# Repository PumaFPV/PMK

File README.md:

# Puma Mechanical Keyboard
PMK - a full wireless HID ecosystem for split keyboards and other fun devices

The goal is to make a suit of wireless devices such as "smart keyboard" (combined mouse and keyboard), gamepad, LEDs, knobs, display, etc  
The first step is to make a wireless split keyboard, and then we will see later...

Currently, you can connect up to 8 (software limited) devices per dongle, each of them having up to 8 (software limited) layers. Layers only affect keyboards and LED.

## Dongle
The dongle is "master" ESP32S2/S3, appears as HID (keyboard, mouse and joystick) and as Mass Storage device Class with config files inside.
Maybe also store password manager later...

As the dongle is the master of PMK, it hosts the config files for each devices. Here is the expected file organisation:

		|--deviceName1  
		|  |- deviceName1.json  
		|  |--keyboard  
		|  |  |- kb-l1.json  
		|  |  |- kb-l2.json  
		|  |--led  
		|  |  |- led-l1.json  
		|  |  |- led-l2.json  
		|--deviceName2  
		|  |- deviceName2.json  
		|  |--keyboard  
		|  |  |- kb-l1.json  
		|  |  |- kb-l2.json  

Exemple file structure can be found [here](https://github.com/PumaFPV/PMK/tree/main/Software/PMK_dongle/data/leftKB) 

For more details about devices configurations / capabilities check the [Protocol](https://github.com/PumaFPV/PMK?tab=readme-ov-file#protocols) chapter.

### Keyboard config file - HID codes
Check out the [PMK HID keyboard keycodes.md](https://github.com/PumaFPV/PMK/blob/main/PMK%20HID%20keyboard%20keycodes.md) for more information on which code corresponds to which key.

## Devices
Can run on any espressif chip that can run ESP-NOW. (I will later add support for nRF52 chips for lower power consumption, but it will be incompatible with ESP32 hardware)
The plan is to run the simplest firmware on all devices and being able to configure them via their corresponding .json files on the master dongle. 
Each device should be configurable via UART (set device ID, set dongle MAC address, and read device MAC address). 
See sample [device code](https://github.com/PumaFPV/PMK/tree/main/Software/PMK_device) for example. (Needs an update)

### Keyboard
For example a keyboard would send pressed keys number "0x04, 0xA1", which the dongle then reads in the .json as coordinates for returning desired key "a,b", if special key is pressed (volume up, brighntess control...) then do the appropriate consummer control action.
Keys are read with 74HC165 shift registers so theoratically you could have A LOT of keys per keyboard. Current limitation is the max value of keyID which is 255, so there could be a maximum of 255 keys per keyboard (+8 layers...).
For more information about the hardawre, check the [hardware](https://github.com/PumaFPV/PMK/tree/main?tab=readme-ov-file#hardware) section.
A casing is being designed, it is 3D printable. As foam grid is put inside for better sound (I think it is better?). 
It support module on the thumb side ([Circle trackpad](https://www.cirque.com/glidepoint-circle-trackpads) and [3D mouse](https://hackaday.io/project/187172-os3m-mouse)). Both modules have been tested and work. See [Space mouse](https://github.com/PumaFPV/PMK/tree/main?tab=readme-ov-file#space-mouse) section for more info.

### Mouse
Mouse can send x,y movement, wheel, pan scrolling and mouse buttons (left, middle, right, forward, backward). Each button is encoded as a bit in the "key" byte of the packet.
No configuration needed on the dongle appart from the DPI setting.
I plan on retro fitting a wired Logitech G300 with PMK so that it frees up a USB port + becomes wireless. It will be a great first POC. I also have a M330 laying around. It might also end up as a PMK mouse.

### Gamepad
Gamepad can send 2 analog joysticks, 2 analog triggers, dpad buttons, and 32 additionnal buttons. No additionnal configuration needed on the dongle.
I current upgraded an old thrustmaster sim set (FCS & WCS) from 1992 with PMK. They used to have an ADB port, but now both are fully wireless and appear as one gamepad on the computer. The update is a bit crude as it was first though as a POC for trying out the gamepad feature. But since it works fine, I kept it this way.

### LED
(For release 1.2.0)
Hopefully processing key press and led function on dongle and send data to device is fast enough, otherwise I will have to run led function on keyboard. (TODO)
Buildin keyboard functions: all kb, breath, swipe wave (single color or rainbow), key wave, single key... (TODO / Partially implemented...)
Uses the WS2812 kind of LED IC.

### Knob
Knobs are in absolute position going from 0 to 255. Could be used for Deej (now only used for deej).

For encoder knobs, this is handled on the device, so it can enumerate as a keyboard pressing one key for clockwise and another for counterclockwise rotation. But it could also be treated as an absolute position depending on the device software.

### Space mouse
The software is mostly inspired from [Magellan](https://github.com/jfedor2/magellan-spacemouse/tree/master) and from reports analysed from a 3DConnexion Space mouse with [hid-tool](https://gitlab.freedesktop.org/libevdev/hid-tools). 
The current electronics and plastics hardware are from [OS3M mouse](https://hackaday.io/project/187172-os3m-mouse) and it works well. The software still needs some adjustements for calibration.
Note: If standard VIK connector is needed, PCB has to be flipped. No special hardware modifications are needed.

## Protocols

### ESP-NOW - Device to Dongle
This is the packet sent via ESP-NOW. 
Packet structure is: 
| Byte | 1 | 2 | 3-16 |
| ---- | - | - | - |
| Description | DeviceID | PacketID | Payload |

The goal of this packet strucure is that the dongle knows who is sending data and what kind of data to expect from the payload.
The deviceID is mostly used for keyboards and mouse to use the corresponding config files.

the payload's goal is to send data as simple as possible, e.g. keyboard sends key IDs pressed (max 8 at a time) and then the dongle processes the key ID depending on the json configuration

| Packet ID | Packet type | Packet information | Number of bytes | Example packet | Example description |
| --------- | ----------- | ------------------ | --------------- | -------------- | ------------------- |
| 0x00 | Telemetry | Send battery voltage, temperature, mac address, errors... | 15 | dID 00 battery temperature address[6] err err err err err |  |
| 0x01 | Keyboard | 1 byte = 1 key ID | 8 | dID 01 A2 34 DB 32 21 4F 00 00 | 6 keys are pressed |
| 0x02 | Mouse | move x, move y, wheel, pan, mouse clicks | 7 | dID 02 xx yy ww pp kk |move x relative, move y relative, move w relative, move p relative, kk key press|
| 0x03 | Gamepad | 2 joysticks, 2 analog triggers, 9 directions d pad, 32 buttons | 12 | dID 03 xx yy zz rz rx ry hh bb bb bb bb bb |  |
| 0x04 | LED | Choose pre defined function, and R, G and B | 8 | dID 04 func ledNumberStart ledNumberEnd Red Green Blue |  |
| 0x05 | Knob / Rotary encoder / potentiometer | each byte is a pot value, max 8 pot per MCU | 10 | dID 05 FF 00 FF 00 FF 00 FF 00 | 4 pots are at max, 4 are at min |
| 0x06 | Actuator | Choose command type (torque, speed, position) | 5 | dID 06 01 |  |
| 0x07 | Display | send image to display using wifi for faster refresh rate? or store on local mem | 6 | dID 07 imgNumber x y brightness | Display img number n at coordinates x,y and brightness b. Might change later |
| 0x08 | Serial | send up to 8 bytes of data | 10 | dID 08 aa bb cc dd ee ff gg hh | Sending 8 bytes of data |
| 0x09 | SpaceMouse | send 3 bytes for translation (x, y, z) and 3 bytes for rotation (x, y, z), signed intergers | 6 | dID 7F 00 00 FF 00 00 | Positive translation on x and negative rotation on x |

### Serial config - Dongle to PC
The dongle supports a few serial commands, they only consist of a string, no CR/LF should be send or the command won't be recongnised. (The received command is hashed into a number then switched cased to the correct function)
Here is the list of supported commands:
  - h / help : display available commands
  - info : display all info
  - macaddress / getmacaddress : display dongle MAC address
  - version : display build date and version
  - power : display RF Tx power
  - cpu : display cpu info
  - format : format file system
  - restart / reboot : restart the dongle
  - deej : toggle on / off deej
  - config / load: Reload configuration files
  - l0 / l1 / l2... : Force the current layer to... If one keybind moves to new layer it will be ignored use l-1 command to reset force layer
  - l-1 : disable forced layer
  - debug1 / debug2... : Toggle debug output. Different kind of debug available

### Serial config - Device to PC
Before being able to communicate with the dongle, the device has to know the dongle MAC address, and must own a deviceID. You will also need to know the device MAC address to give it to the dongle.
Here is the list of supported commands:
- h / help : returns available commands
- info : display all info
- macaddress / getmacaddress : returns device MAC address
- setdonglemacaddress : update dongle MAC address, be sure to send values in HEX mode
- getdonglemacaddress : returns the current dongle MAC address
- setdeviceid : update deviceID to new value
- getdeviceid : returns currently set devi
- version : returns build date and version
- power : returns RF Tx power
- cpu : returns CPU info
- setcpufreq : set new CPU frequency
- restart : restart the dongle
- scan : Scan for side module presence
- debug1 / debug2... : Toggle debug output. Different kind of debug available

## Hardware
### The dongle
Dongle is still HW00 (first rev), it needs 3 small patches to work properly. A [HW01](https://github.com/PumaFPV/PMK/tree/main/Hardware/PMK_Dongle/PMK_Dongle_HW01) is designed but hasn't been ordered yet.
The ESP32S2 has some limitations, so a ESP32S3 dongle is being made too [here](https://github.com/PumaFPV/PMK/tree/main/Hardware/PMK_Dongle/PMK_Dongle_S3_HW00).

Even a nRF52 dongle might be made... Who knows[?](https://github.com/PumaFPV/PMK/tree/main/Hardware/PMK_Dongle/PMK_Dongle_C_nRF_HW00)

### The keyboard
As of today the keyboard is at the HW02 stage, and uses the sofle layout (which I do like). It uses 29 hot swappable Kailh Choc switches + one rotary encoder. The MCU is a [PSoM module](https://github.com/PumaFPV/PSoM) (homemade SoM) with an ESP32S2 inside. The SoM allows for quick swap of different MCU to try out different feature. Today the ESP32S2 is used for the ease of software developpement. Its power consumption is bad I am aware. But at least software works.
Here is the changelog.

| HW rev | change list |
| ------ | ----------- |
| HW00   | Based on moonlander layout, integrated ESP32, used as a proof of concept, didn't like the layout in the end |
| HW01   | Based on Sofle, PSoM connector (swappable uC for futur proofing), added rotary encoder, way better layout in my opinion. Added side connector option for trackpad or space mouse |
| HW02   | Still soffle, added support for kailh choc V2 (failed), moved the rotary encoder up, added debouncing for rotary encoder, fixed the side module connector, moved test point to accessible location, updated PSoM pinout for better compatibility |
| HW03 (WIP)  | Still soffle, fixed the silkscreen, Added slot for dongle, fixed V2 footprint, magnetic pogo module? |

More info on [Notion](https://swamp-zydeco-907.notion.site/PumaKeyBoard-b41d42fec8c74b02bc73637fae3648d7)

### Edit the PCBs
If you want to make your own keyboard, or visualize current dongle, keyboard or other devices you will need KiCAD 8 and Component_lib which is my own components library. It can be found in its [own repo](https://github.com/PumaFPV/Component_lib), information on own to install it can be found there.

# Building 
This whole project is built using PlatformIO on VS Code / VS Codium. (If using VS Codium note that the marketplace for extensions doesn't really work, you will need to download cpp and platformIO .vsix extension files from https://marketplace.visualstudio.com/vscode)

Once this is installed you can clone PMK's repo ````git clone https://github.com/PumaFPV/PMK````
and open whichever code you want to build / modify: ````PMK/Software/PMK_keyboard```` with platformIO "Open project".

Once project is opened and loaded (might take a few minutes for the first time) (it needs internet connection to download library and toolchain) you can compile with ````ctrl + shift + B```` or ````ctrl + shift + U```` to compile and upload, or use the bottom ribbon (make sure to select the correct workspace before compiling and uploading).

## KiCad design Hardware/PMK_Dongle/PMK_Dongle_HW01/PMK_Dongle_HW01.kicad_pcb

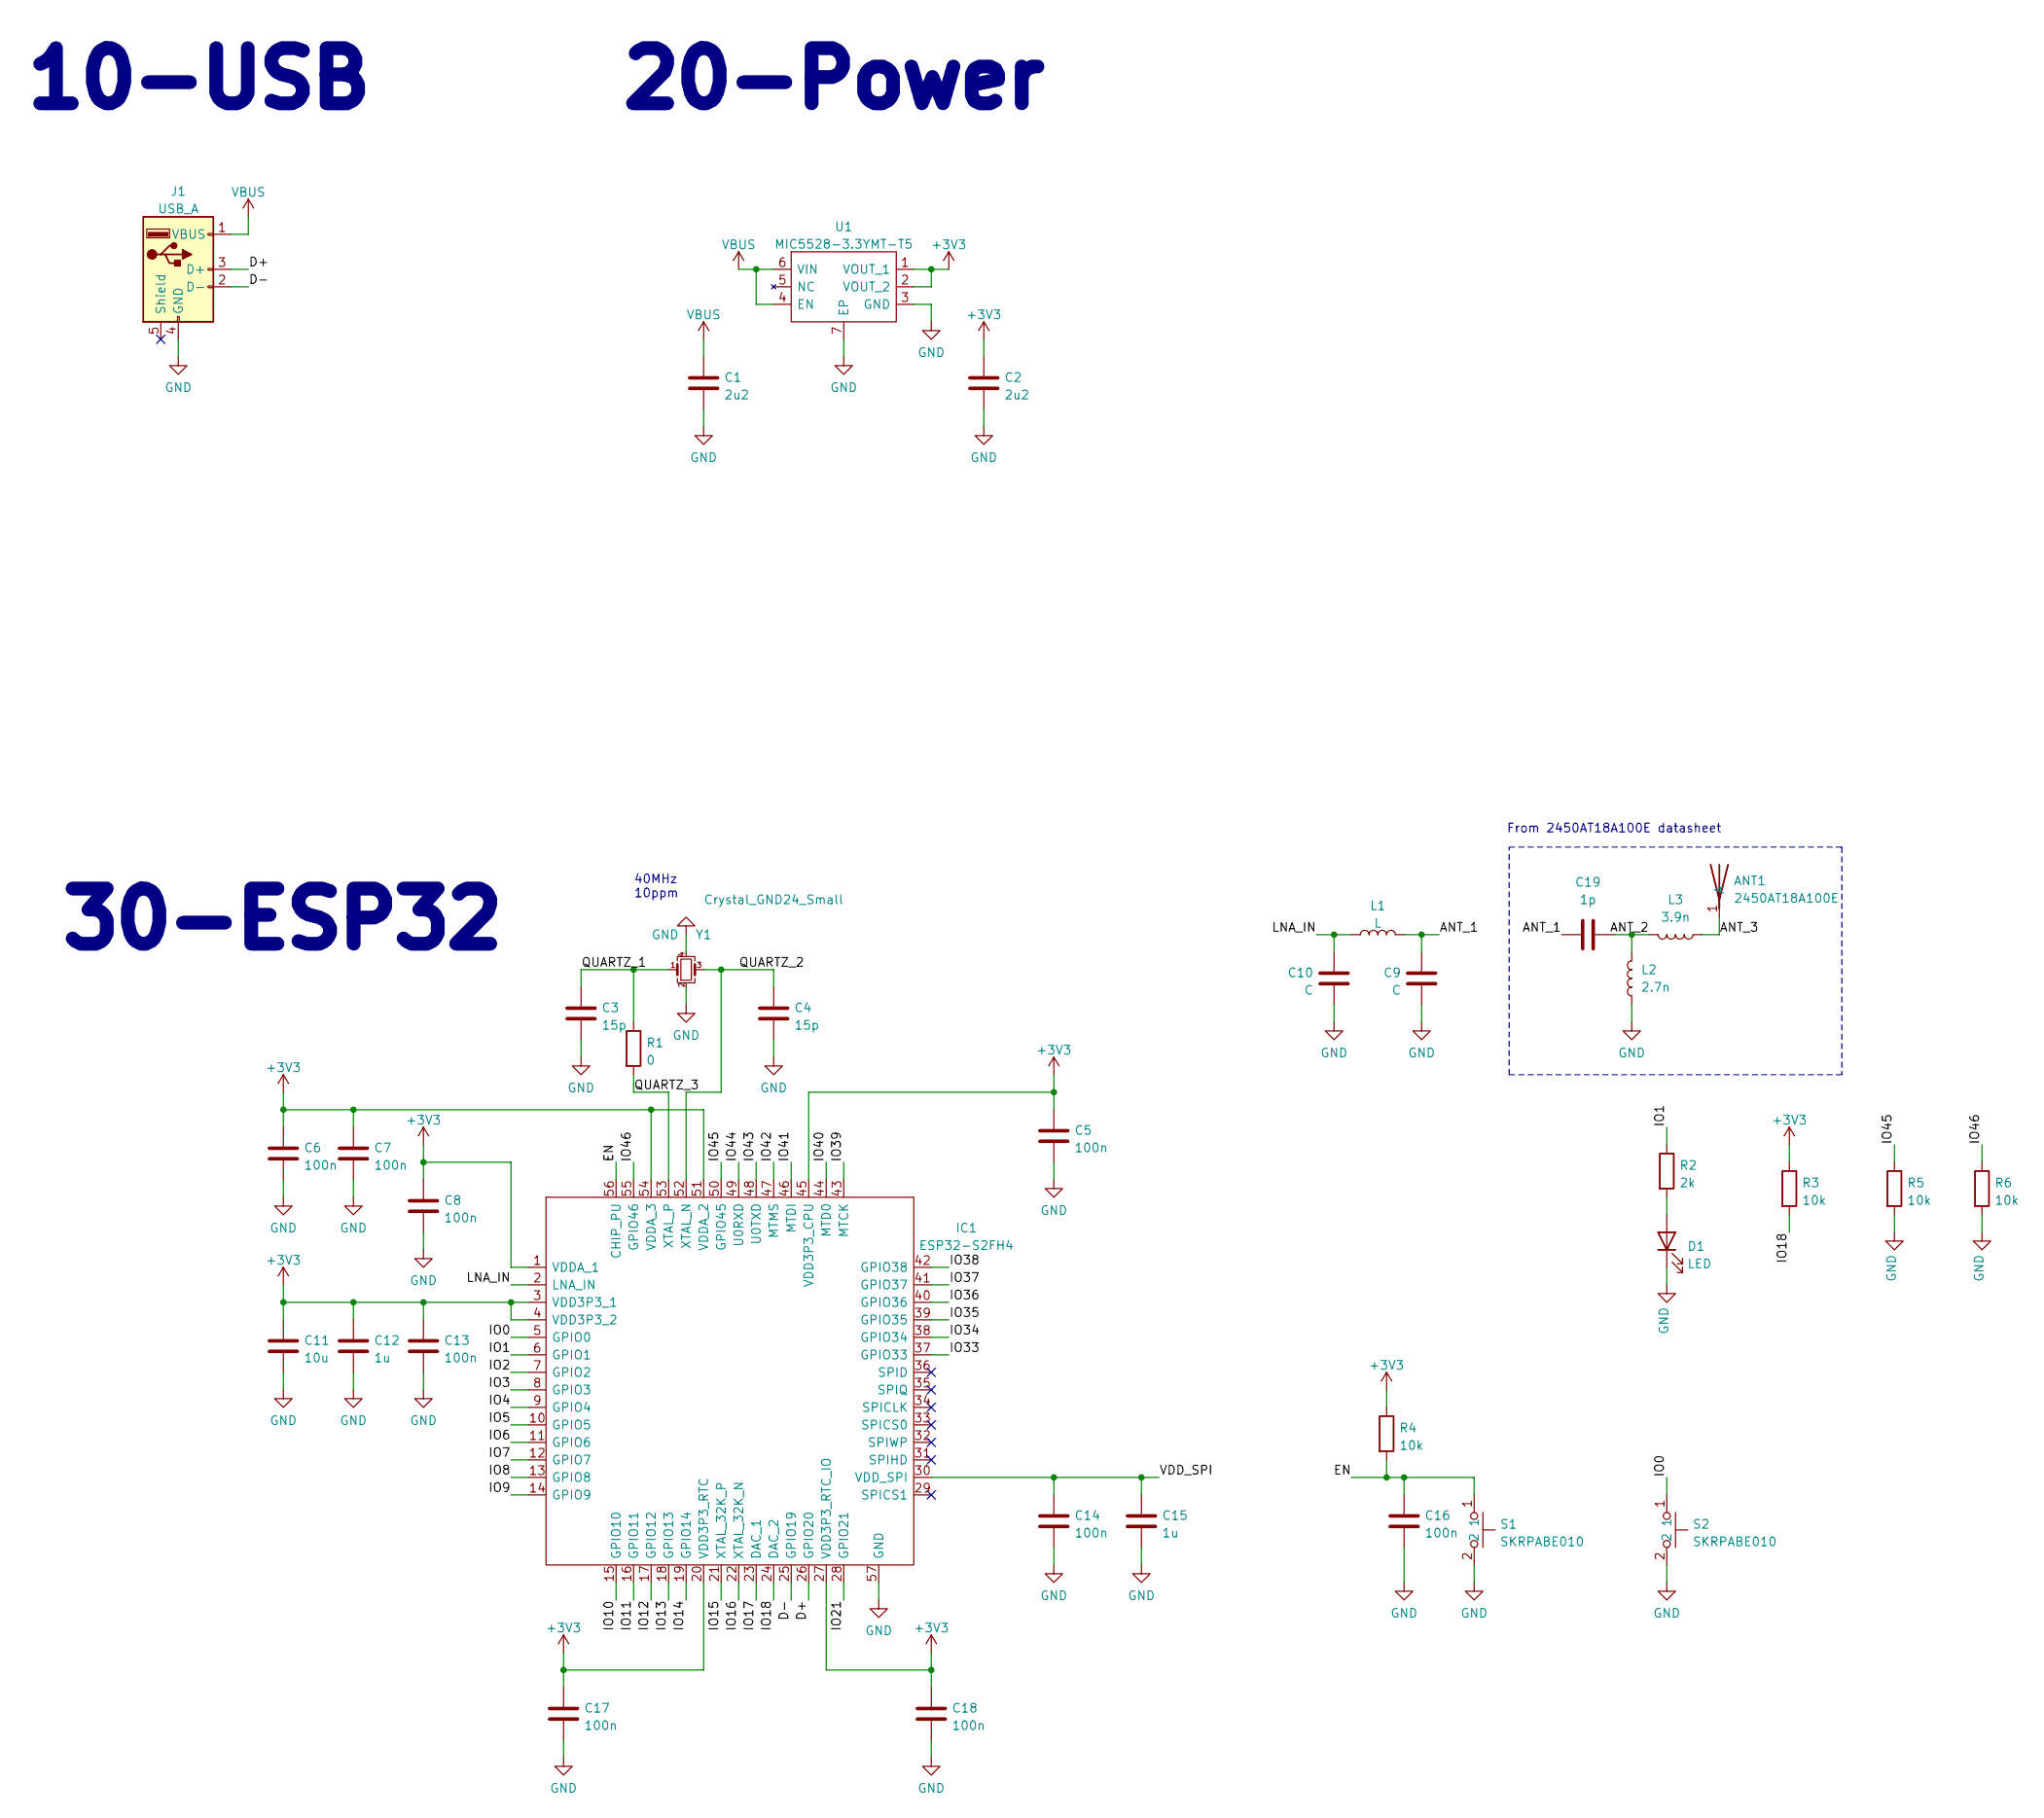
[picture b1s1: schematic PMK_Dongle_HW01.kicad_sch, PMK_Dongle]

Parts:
ANT1: 2450AT18A100E; ANTC3216X140N; Mouser Part Number 609-2450AT18A100E
C1, C2: 2u2; C_0603_1608Metric
C3, C4: 15p; C_0201_0603Metric
C5, C6, C7, C8, C13, C14, C16, C17, C18: 100n; C_0402_1005Metric
C9, C10: C; C_0201_0603Metric
C11: 10u; C_0603_1608Metric
C12, C15: 1u; C_0402_1005Metric
C19: 1p; C_0402_1005Metric
D1: LED; LED_0402_1005Metric
IC1: ESP32-S2FH4; QFN40P700X700X90-57N-D; Mouser Part Number 356-ESP32-S2FH4
J1: USB_A; USB_PCB
L1: L; L_0201_0603Metric
L2: 2.7n; L_0402_1005Metric
L3: 3.9n; L_0402_1005Metric
R1: 0; R_0201_0603Metric
R2: 2k; R_0402_1005Metric
R3, R4, R5, R6: 10k; R_0201_0603Metric
S1, S2: SKRPABE010; B3U-1000P; Mouser Part Number 688-SKRPAB
U1: MIC5528-3.3YMT-T5; SON40P120X120X60-7N-D; Mouser Part Number 998-MIC5528-3.3YMTT5
Y1: Crystal_GND24_Small; Crystal_SMD_2016-4Pin_2.0x1.6mm

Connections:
+3V3: C2.1, C5.1, C6.1, C7.1, C8.1, C11.1, C12.1, C13.1, C17.1, C18.1, IC1.1 (VDDA_1), IC1.3 (VDD3P3_1), IC1.4 (VDD3P3_2), IC1.20 (VDD3P3_RTC), IC1.27 (VDD3P3_RTC_IO), IC1.45 (VDD3P3_CPU), IC1.51 (VDDA_2), IC1.54 (VDDA_3), R3.1, R4.1, U1.1 (VOUT_1), U1.2 (VOUT_2)
/ANT_1: C9.1, C19.2, L1.1
/ANT_2: C19.1, L2.1, L3.1
/ANT_3: ANT1.1 (A), L3.2
/D+: IC1.26 (GPIO20), J1.3 (D+)
/D-: IC1.25 (GPIO19), J1.2 (D-)
/EN: C16.1, IC1.56 (CHIP_PU), R4.2, S1.1
/IO0: IC1.5 (GPIO0), S2.1
/IO1: IC1.6 (GPIO1), R2.1
/IO2: IC1.7 (GPIO2)
/IO3: IC1.8 (GPIO3)
/IO4: IC1.9 (GPIO4)
/IO5: IC1.10 (GPIO5)
/IO6: IC1.11 (GPIO6)
/IO7: IC1.12 (GPIO7)
/IO8: IC1.13 (GPIO8)
/IO9: IC1.14 (GPIO9)
/IO10: IC1.15 (GPIO10)
/IO11: IC1.16 (GPIO11)
/IO12: IC1.17 (GPIO12)
/IO13: IC1.18 (GPIO13)
/IO14: IC1.19 (GPIO14)
/IO15: IC1.21 (XTAL_32K_P)
/IO16: IC1.22 (XTAL_32K_N)
/IO17: IC1.23 (DAC_1)
/IO18: IC1.24 (DAC_2), R3.2
/IO21: IC1.28 (GPIO21)
/IO33: IC1.37 (GPIO33)
/IO34: IC1.38 (GPIO34)
/IO35: IC1.39 (GPIO35)
/IO36: IC1.40 (GPIO36)
/IO37: IC1.41 (GPIO37)
/IO38: IC1.42 (GPIO38)
/IO39: IC1.43 (MTCK)
/IO40: IC1.44 (MTD0)
/IO41: IC1.46 (MTDI)
/IO42: IC1.47 (MTMS)
/IO43: IC1.48 (U0TXD)
/IO44: IC1.49 (U0RXD)
/IO45: IC1.50 (GPIO45), R5.1
/IO46: IC1.55 (GPIO46), R6.1
/LNA_IN: C10.1, IC1.2 (LNA_IN), L1.2
/QUARTZ_1: C3.1, R1.1, Y1.1
/QUARTZ_2: C4.1, IC1.52 (XTAL_N), Y1.3
/QUARTZ_3: IC1.53 (XTAL_P), R1.2
/VDD_SPI: C14.1, C15.1, IC1.30 (VDD_SPI)
GND: C1.2, C2.2, C3.2, C4.2, C5.2, C6.2, C7.2, C8.2, C9.2, C10.2, C11.2, C12.2, C13.2, C14.2, C15.2, C16.2, C17.2, C18.2, D1.1 (K), IC1.57 (GND), J1.4 (GND), L2.2, R5.2, R6.2, S1.2, S2.2, U1.3 (GND), U1.7 (EP), Y1.2, Y1.4
unnamed: D1.2 (A), R2.2
VBUS: C1.1, J1.1 (VBUS), U1.4 (EN), U1.6 (VIN)

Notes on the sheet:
From 2450AT18A100E datasheet
10-USB
30-ESP32
40MHz 10ppm
20-Power

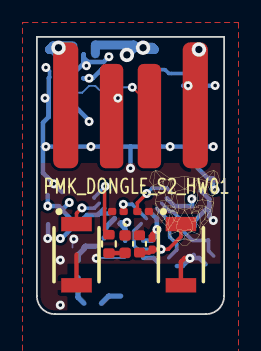
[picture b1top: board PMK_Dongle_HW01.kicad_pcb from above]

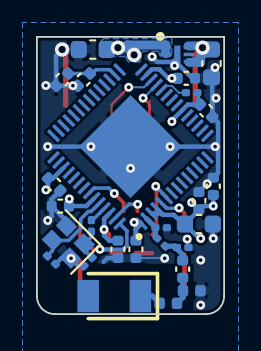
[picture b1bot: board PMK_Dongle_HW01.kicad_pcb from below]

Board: 4 copper layers, 10.4 x 15.4 mm, 36 parts (27 on the bottom side), 20 nets.

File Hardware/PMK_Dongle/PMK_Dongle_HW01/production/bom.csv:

Designator,Footprint,Quantity,Value,LCSC Part #
ANT1,ANTC3216X140N,1,2450AT18A100E,
C1,0603,1,10u,
C10,0201,1,C,
C11,0603,1,10u,
C12,0402,1,1u,
C13,0402,1,100n,
C14,0402,1,100n,
C15,0402,1,1u,
C16,0402,1,100n,
C17,0402,1,100n,
C18,0402,1,100n,
C2,0603,1,10u,
C3,0201,1,15p,
C4,0201,1,15p,
C5,0402,1,100n,
C6,0402,1,100n,
C7,0402,1,100n,
C8,0402,1,100n,
C9,0201,1,C,
D1,0402,1,LED,
IC1,QFN40P700X700X90-57N-D,1,ESP32-S2FH4,
J1,USB_PCB,1,USB_A,
L1,0201,1,L,
R1,0201,1,0,
R2,0402,1,2k,
R3,0201,1,10k,
R4,0402,1,10k,
"S1, S2",SKRPABE010,2,SKRPABE010,
U1,SON40P120X120X60-7N-D,1,MIC5528-3.3YMT-T5,
Y1,Crystal_SMD_2016-4Pin_2.0x1.6mm,1,Crystal_GND24_Small,

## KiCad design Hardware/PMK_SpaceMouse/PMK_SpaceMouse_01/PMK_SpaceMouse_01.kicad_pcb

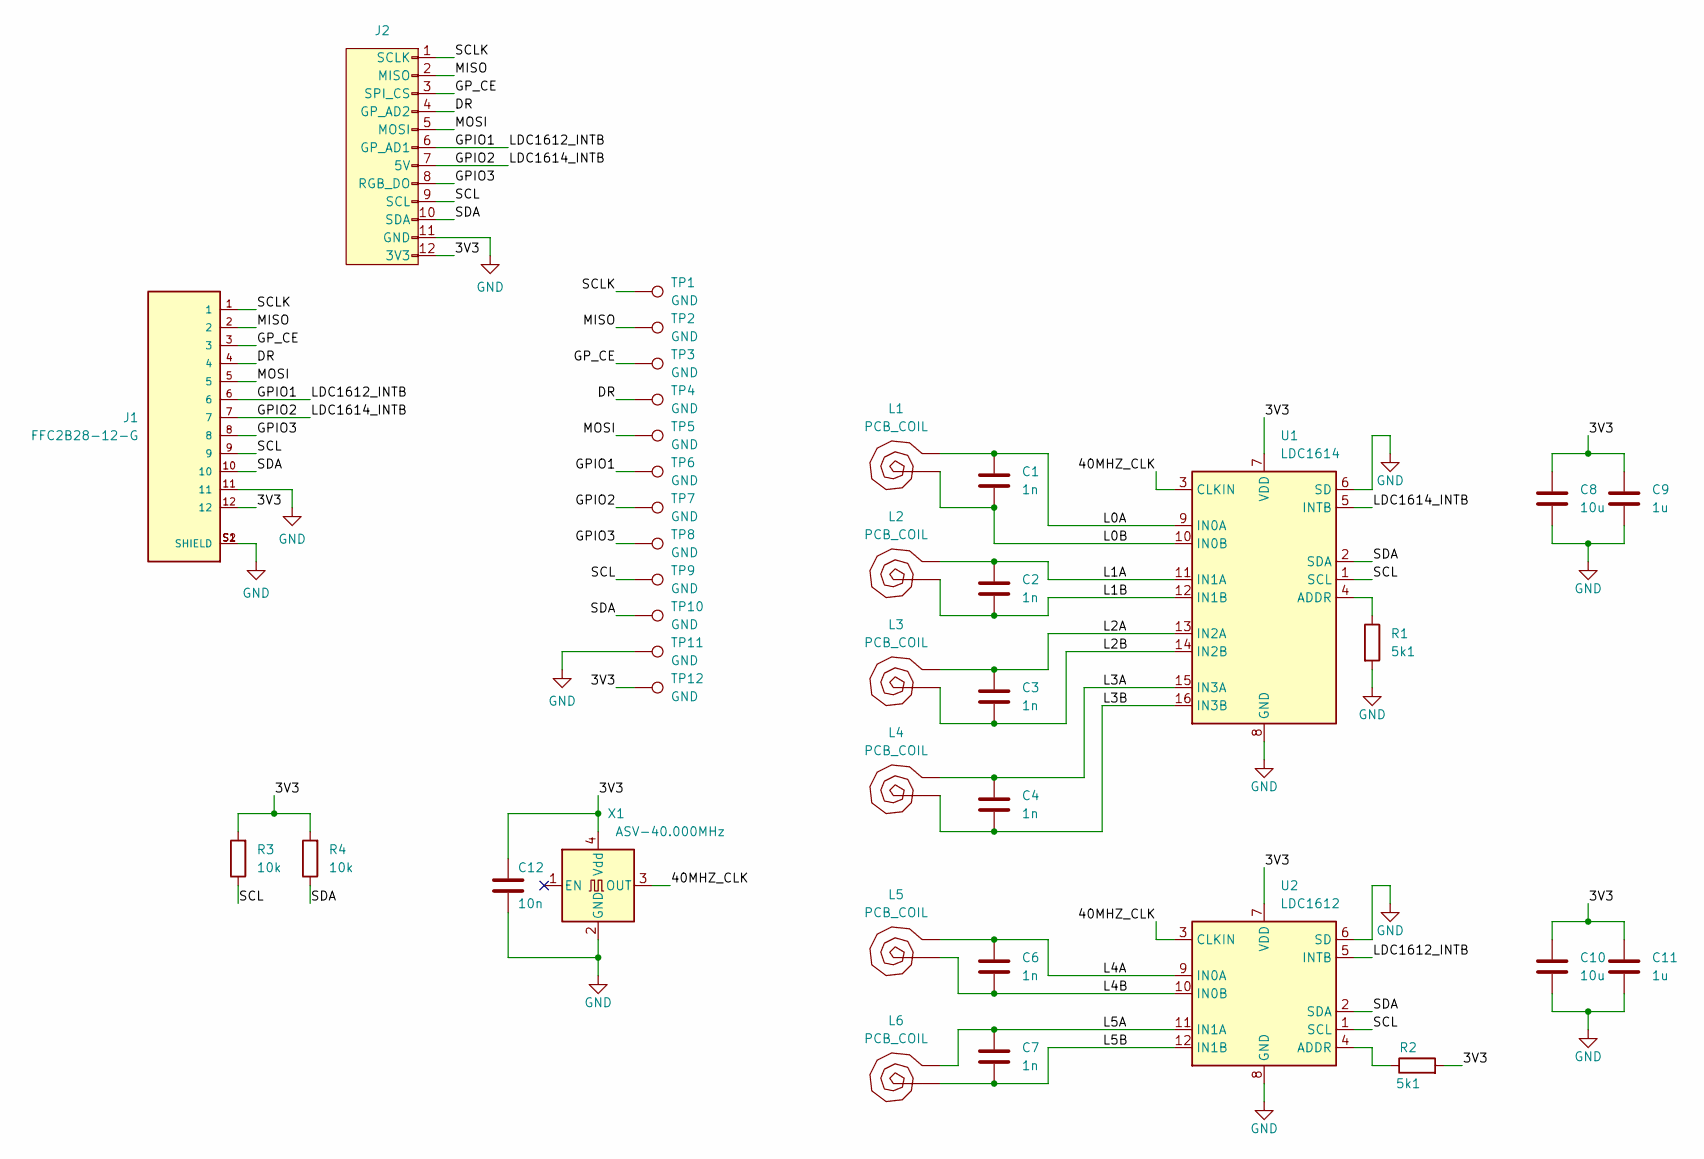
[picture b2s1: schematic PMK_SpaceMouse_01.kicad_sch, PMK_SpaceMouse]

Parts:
C1, C2, C3, C4, C6, C7: 1n; C_0402_1005Metric
C8, C10: 10u; C_0402_1005Metric
C9, C11: 1u; C_0402_1005Metric
C12: 10n; C_0402_1005Metric
J1: FFC2B28-12-G; GCT_FFC2B28-12-G; PARTREV A; DigiKey_Part_Number 2073-FFC2B28-12-GTR-ND
J2: vik-module-connector; vik-module-connector-horizontal
L1, L2, L3, L4, L5, L6: PCB_COIL; COIL_PCB
R1, R2: 5k1; R_0402_1005Metric
R3, R4: 10k; R_0402_1005Metric
TP1, TP2, TP3, TP4, TP5, TP6, TP7, TP8, TP9, TP10, TP11, TP12: GND; TestPoint_Pad_D1.5mm
U1: LDC1614; WQFN-16-1EP_4x4mm_P0.5mm_EP2.6x2.6mm
U2: LDC1612; WSON-12-1EP_4x4mm_P0.5mm_EP2.6x3mm
X1: ASV-40.000MHz; Oscillator_SMD_Abracon_ASV-4Pin_7.0x5.1mm

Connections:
/3V3: C8.1, C9.1, C10.1, C11.1, C12.1, J1.12, J2.12 (3V3), R2.2, R3.2, R4.2, TP12.1, U1.7 (VDD), U2.7 (VDD), X1.4 (Vdd)
/40MHZ_CLK: U1.3 (CLKIN), U2.3 (CLKIN), X1.3 (OUT)
/DR: J1.4, J2.4 (GP_AD2), TP4.1
/GPIO1: J1.6, J2.6 (GP_AD1), TP6.1, U2.5 (INTB)
/GPIO2: J1.7, J2.7 (5V), TP7.1, U1.5 (INTB)
/GPIO3: J1.8, J2.8 (RGB_DO), TP8.1
/GP_CE: J1.3, J2.3 (SPI_CS), TP3.1
/L0A: C1.1, L1.1, U1.9 (IN0A)
/L0B: C1.2, L1.2, U1.10 (IN0B)
/L1A: C2.1, L2.1, U1.11 (IN1A)
/L1B: C2.2, L2.2, U1.12 (IN1B)
/L2A: C3.1, L3.1, U1.13 (IN2A)
/L2B: C3.2, L3.2, U1.14 (IN2B)
/L3A: C4.1, L4.1, U1.15 (IN3A)
/L3B: C4.2, L4.2, U1.16 (IN3B)
/L4A: C6.1, L5.1, U2.9 (IN0A)
/L4B: C6.2, L5.2, U2.10 (IN0B)
/L5A: C7.1, L6.1, U2.11 (IN1A)
/L5B: C7.2, L6.2, U2.12 (IN1B)
/MISO: J1.2, J2.2 (MISO), TP2.1
/MOSI: J1.5, J2.5 (MOSI), TP5.1
/SCL: J1.9, J2.9 (SCL), R3.1, TP9.1, U1.1 (SCL), U2.1 (SCL)
/SCLK: J1.1, J2.1 (SCLK), TP1.1
/SDA: J1.10, J2.10 (SDA), R4.1, TP10.1, U1.2 (SDA), U2.2 (SDA)
GND: C8.2, C9.2, C10.2, C11.2, C12.2, J1.11, J1.S1 (SHIELD), J1.S2 (SHIELD), J2.11 (GND), R1.2, TP11.1, U1.6 (SD), U1.8 (GND), U1.17 (GND), U2.6 (SD), U2.8 (GND), U2.13 (GND), X1.2 (GND)
unnamed: R1.1, U1.4 (ADDR)
unnamed: R2.1, U2.4 (ADDR)

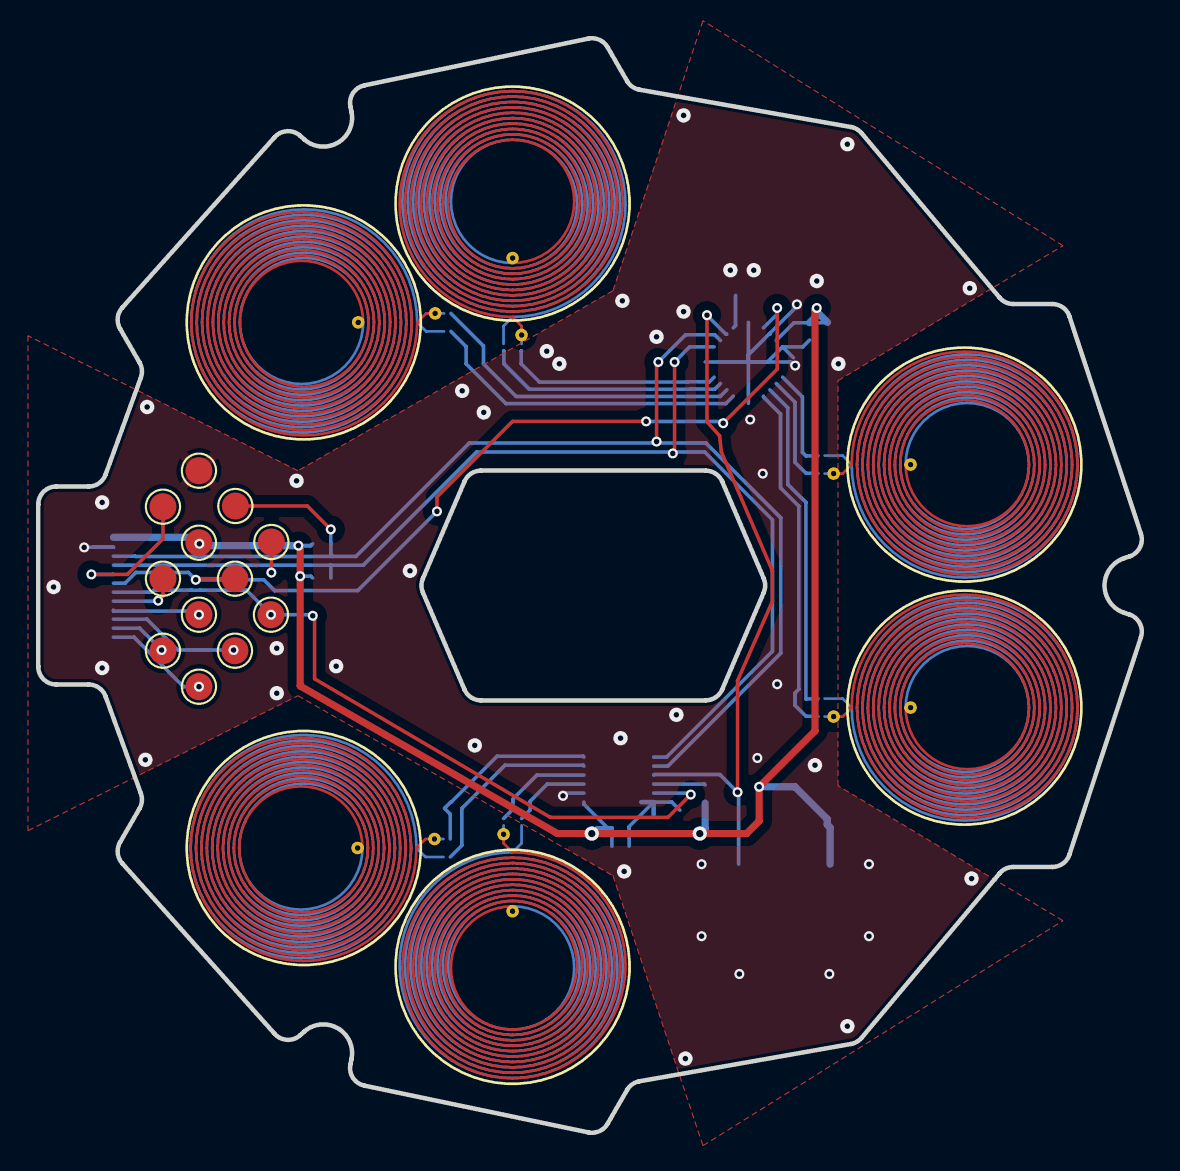
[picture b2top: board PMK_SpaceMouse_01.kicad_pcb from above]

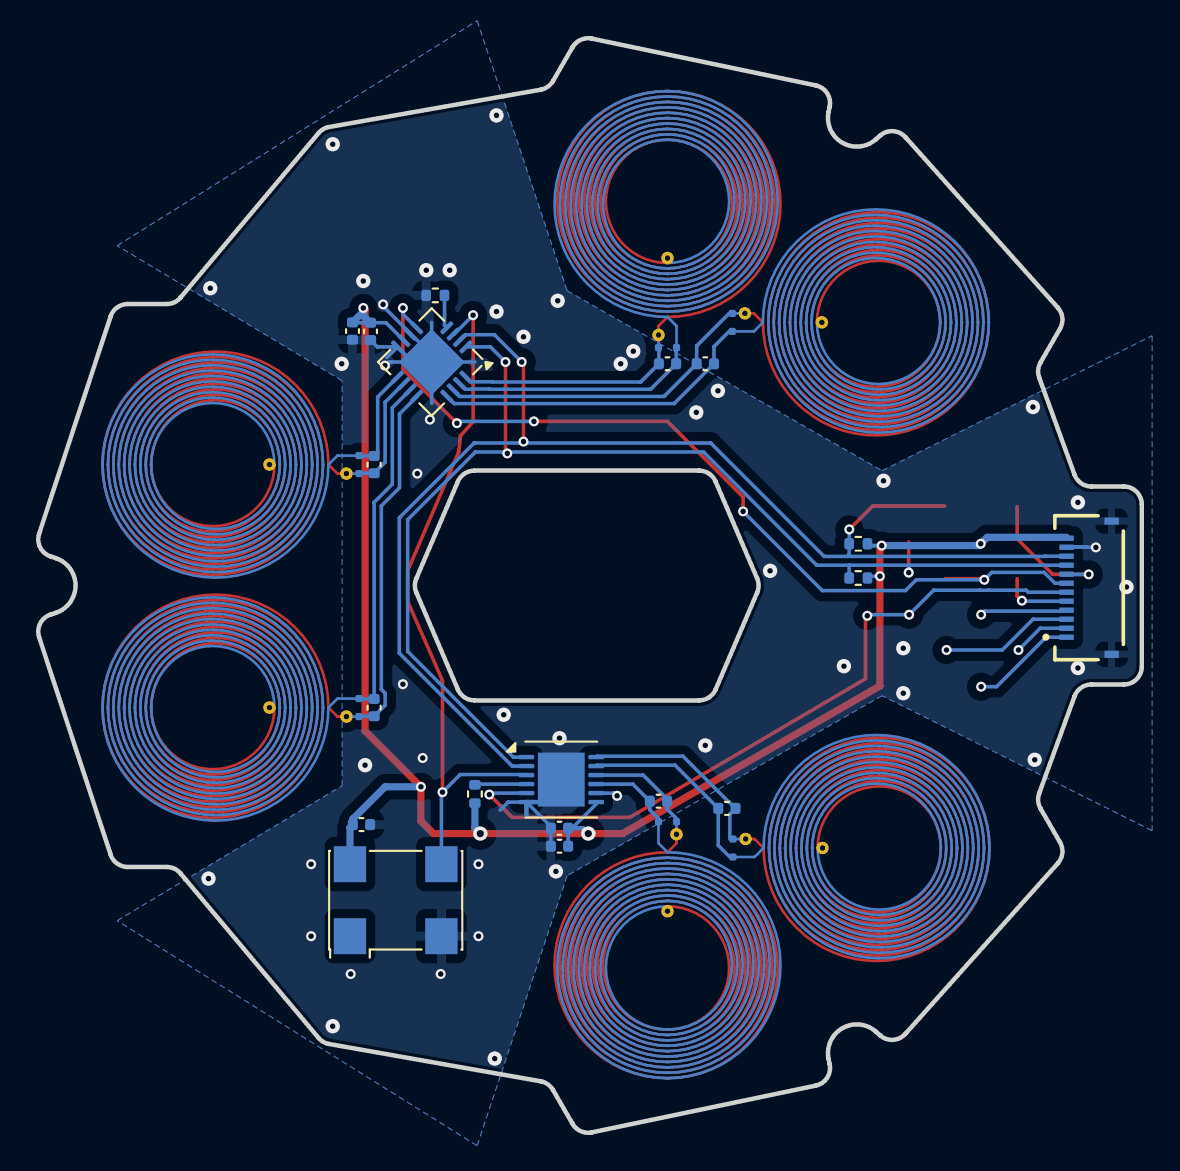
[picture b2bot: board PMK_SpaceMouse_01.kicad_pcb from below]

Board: 2 copper layers, 61.3 x 60.8 mm, 37 parts (25 on the bottom side), 27 nets.

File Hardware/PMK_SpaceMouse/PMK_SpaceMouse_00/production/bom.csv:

Designator,Footprint,Quantity,Value,LCSC Part #
"C1, C2, C3, C4, C6, C7",0402,6,1n,
"C10, C8",0402,2,10u,
"C11, C9",0402,2,1u,
C12,0402,1,10n,
J1,GCT_FFC2B28-12-G,1,FFC2B28-12-G,
"L1, L2, L3, L4, L5, L6",COIL_PCB,6,PCB_COIL,
"R1, R2",0402,2,5k1,
"R3, R4",0402,2,10k,
"TP1, TP10, TP11, TP12, TP2, TP3, TP4, TP5, TP6, TP7, TP8, TP9",TestPoint_Pad_D1.5mm,12,GND,
U1,WQFN-16-1EP_4x4mm_P0.5mm_EP2.6x2.6mm,1,LDC1614,
U2,WSON-12-1EP_4x4mm_P0.5mm_EP2.6x3mm,1,LDC1612,
X1,Oscillator_SMD_Abracon_ASV-4Pin_7.0x5.1mm,1,ASV-40.000MHz,

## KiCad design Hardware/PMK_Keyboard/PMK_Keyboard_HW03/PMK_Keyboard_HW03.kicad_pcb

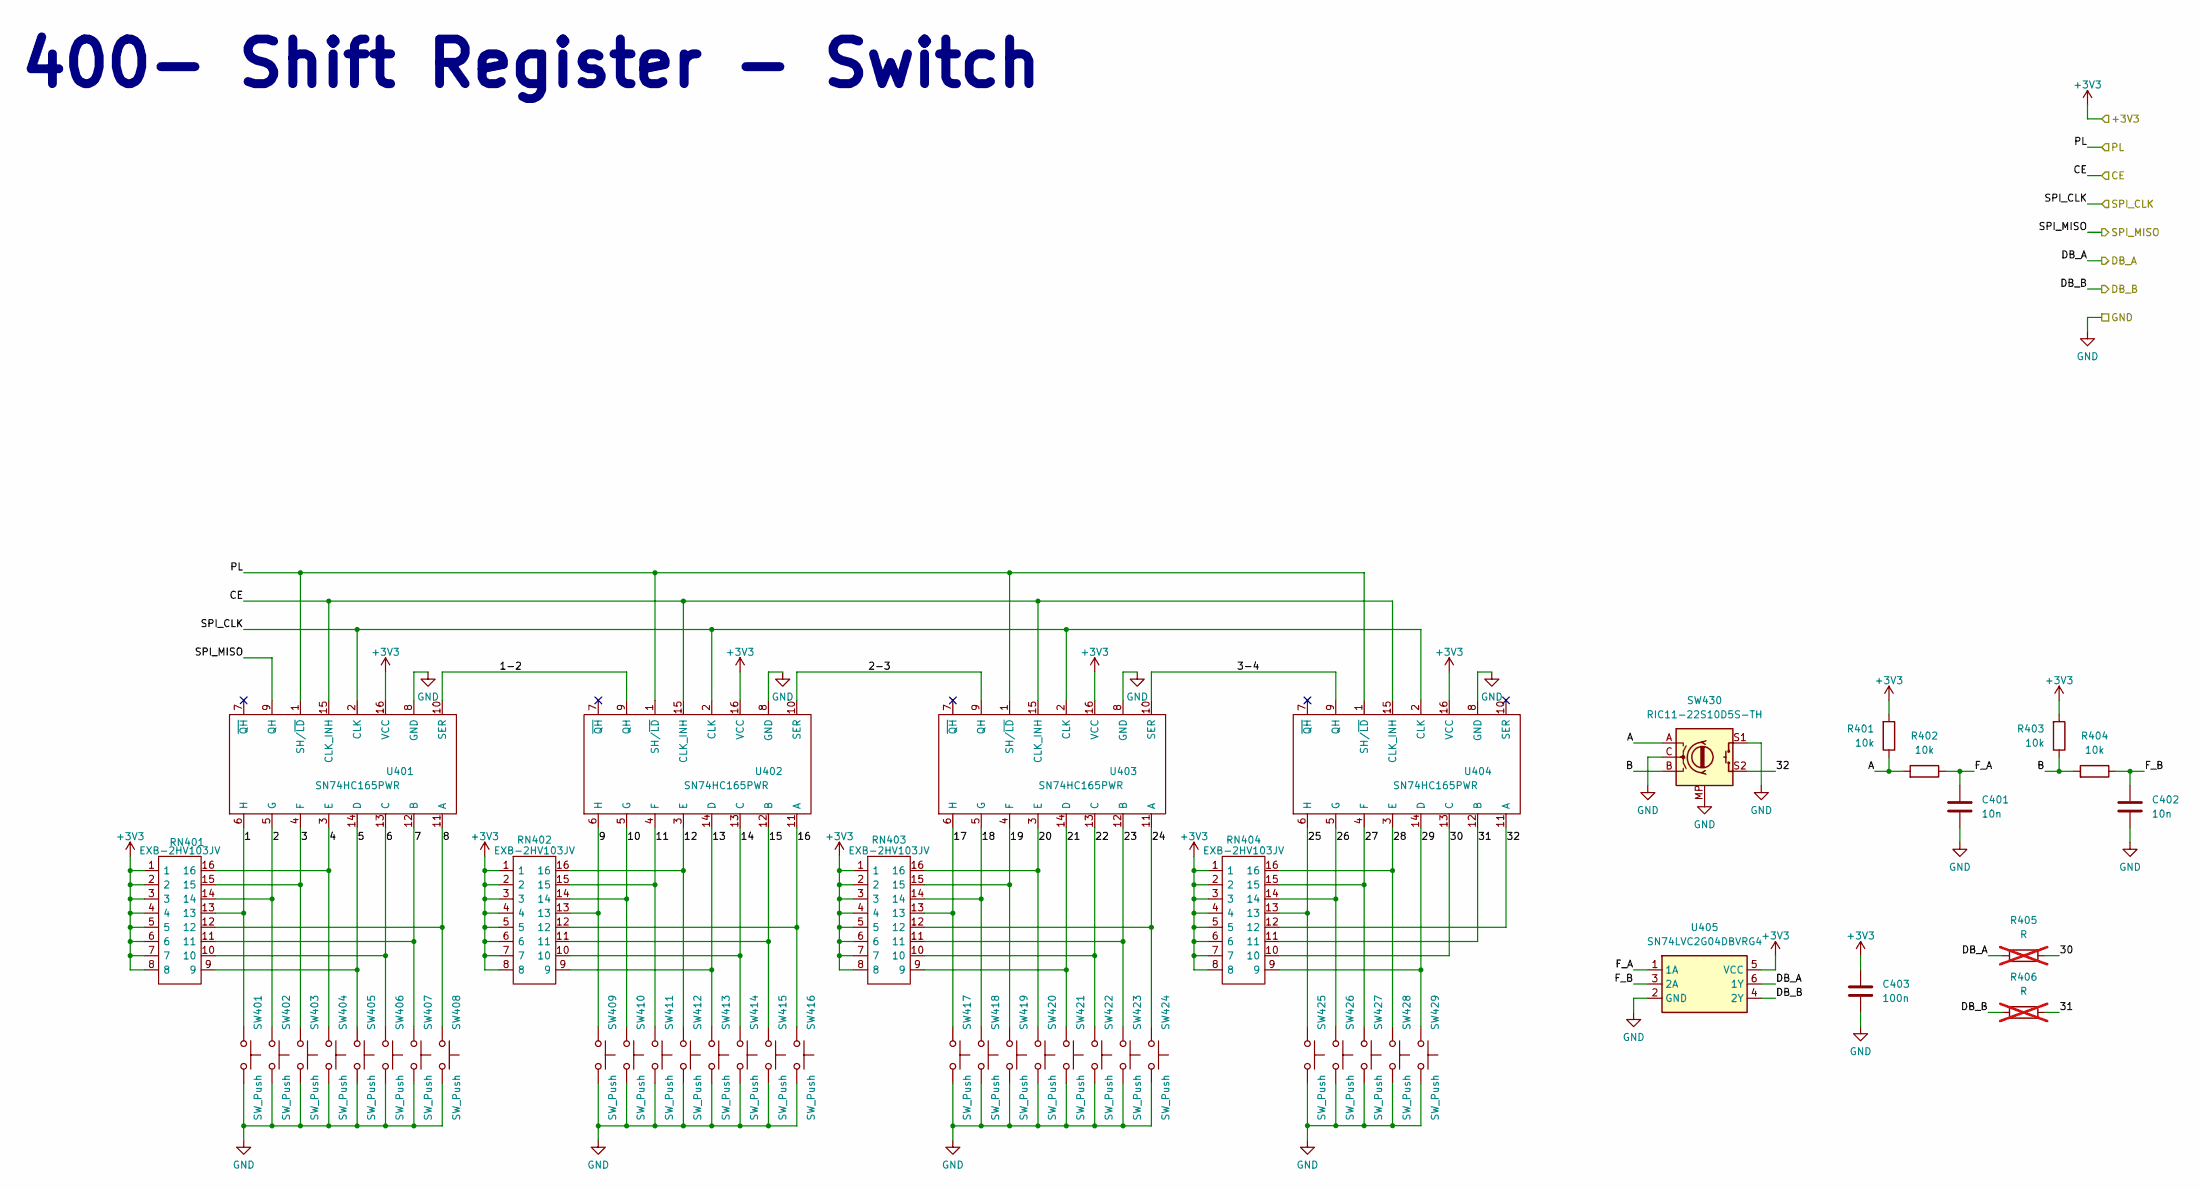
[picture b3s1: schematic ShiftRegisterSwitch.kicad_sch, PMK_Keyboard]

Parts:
C401, C402: 10n; C_0402_1005Metric
C403: 100n; C_0402_1005Metric
R401, R402, R403, R404: 10k; R_0201_0603Metric
R405, R406: R; R_0402_1005Metric; not fitted
RN401, RN402, RN403, RN404: EXB-2HV103JV; EXB2HV_1; Mouser Part Number 667-EXB-2HV103JV
SW401, SW402, SW403, SW404, SW405, SW406, SW407, SW408, SW409, SW410, SW411, SW412, SW413, SW414, SW415, SW416, SW417, SW418, SW419, SW420, SW421, SW422, SW423, SW424, SW425, SW426, SW427, SW428, SW429: SW_Push; Kailh_socket_PG1350_reversible_V1V2
SW430: RIC11-22S10D5S-TH
U401, U402, U403, U404: SN74HC165PWR; SOP65P640X120-16N; Mouser Part Number 595-SN74HC165PWR
U405: SN74LVC2G04DBVRG4; SOP95P280X145-6N; Mouser Part Number 595-74LVC2G04DBVRG4

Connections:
+3V3: C403.1, R401.2, R403.2, RN401.1, RN401.2, RN401.3, RN401.4, RN401.5, RN401.6, RN401.7, RN401.8, RN402.1, RN402.2, RN402.3, RN402.4, RN402.5, RN402.6, RN402.7, RN402.8, RN403.1, RN403.2, RN403.3, RN403.4, RN403.5, RN403.6, RN403.7, RN403.8, RN404.1, RN404.2, RN404.3, RN404.4, RN404.5, RN404.6, RN404.7, RN404.8, U401.16 (VCC), U402.16 (VCC), U403.16 (VCC), U404.16 (VCC), U405.5 (VCC); also elsewhere on the board
/200- PSoM/DB_A: R405.1, U405.6 (1Y); also elsewhere on the board
/200- PSoM/DB_B: R406.1, U405.4 (2Y); also elsewhere on the board
/200- PSoM/PL: U401.1 (SH/~LD), U402.1 (SH/~LD), U403.1 (SH/~LD), U404.1 (SH/~LD); also elsewhere on the board
/200- PSoM/SPI_CLK: U401.2 (CLK), U402.2 (CLK), U403.2 (CLK), U404.2 (CLK); also elsewhere on the board
/200- PSoM/SPI_MISO: U401.9 (QH); also elsewhere on the board
/200- PSoM/SR_CE: U401.15 (CLK_INH), U402.15 (CLK_INH), U403.15 (CLK_INH), U404.15 (CLK_INH); also elsewhere on the board
/400- Shift Register - Switch/1: RN401.13, SW401.1, U401.6 (H)
/400- Shift Register - Switch/1-2: U401.10 (SER), U402.9 (QH)
/400- Shift Register - Switch/2: RN401.14, SW402.1, U401.5 (G)
/400- Shift Register - Switch/2-3: U402.10 (SER), U403.9 (QH)
/400- Shift Register - Switch/3: RN401.15, SW403.1, U401.4 (F)
/400- Shift Register - Switch/3-4: U403.10 (SER), U404.9 (QH)
/400- Shift Register - Switch/4: RN401.16, SW404.1, U401.3 (E)
/400- Shift Register - Switch/5: RN401.9, SW405.1, U401.14 (D)
/400- Shift Register - Switch/6: RN401.10, SW406.1, U401.13 (C)
/400- Shift Register - Switch/7: RN401.11, SW407.1, U401.12 (B)
/400- Shift Register - Switch/8: RN401.12, SW408.1, U401.11 (A)
/400- Shift Register - Switch/9: RN402.13, SW409.1, U402.6 (H)
/400- Shift Register - Switch/10: RN402.14, SW410.1, U402.5 (G)
/400- Shift Register - Switch/11: RN402.15, SW411.1, U402.4 (F)
/400- Shift Register - Switch/12: RN402.16, SW412.1, U402.3 (E)
/400- Shift Register - Switch/13: RN402.9, SW413.1, U402.14 (D)
/400- Shift Register - Switch/14: RN402.10, SW414.1, U402.13 (C)
/400- Shift Register - Switch/15: RN402.11, SW415.1, U402.12 (B)
/400- Shift Register - Switch/16: RN402.12, SW416.1, U402.11 (A)
/400- Shift Register - Switch/17: RN403.13, SW417.1, U403.6 (H)
/400- Shift Register - Switch/18: RN403.14, SW418.1, U403.5 (G)
/400- Shift Register - Switch/19: RN403.15, SW419.1, U403.4 (F)
/400- Shift Register - Switch/20: RN403.16, SW420.1, U403.3 (E)
/400- Shift Register - Switch/21: RN403.9, SW421.1, U403.14 (D)
/400- Shift Register - Switch/22: RN403.10, SW422.1, U403.13 (C)
/400- Shift Register - Switch/23: RN403.11, SW423.1, U403.12 (B)
/400- Shift Register - Switch/24: RN403.12, SW424.1, U403.11 (A)
/400- Shift Register - Switch/25: RN404.13, SW425.1, U404.6 (H)
/400- Shift Register - Switch/26: RN404.14, SW426.1, U404.5 (G)
/400- Shift Register - Switch/27: RN404.15, SW427.1, U404.4 (F)
/400- Shift Register - Switch/28: RN404.16, SW428.1, U404.3 (E)
/400- Shift Register - Switch/29: RN404.9, SW429.1, U404.14 (D)
/400- Shift Register - Switch/30: R405.2, RN404.10, U404.13 (C)
/400- Shift Register - Switch/31: R406.2, RN404.11, U404.12 (B)
/400- Shift Register - Switch/32: RN404.12, SW430.S2, U404.11 (A)
/400- Shift Register - Switch/A: R401.1, R402.2, SW430.A
/400- Shift Register - Switch/B: R403.1, R404.2, SW430.B
/400- Shift Register - Switch/F_A: C401.1, R402.1, U405.1 (1A)
/400- Shift Register - Switch/F_B: C402.1, R404.1, U405.3 (2A)
GND: C401.2, C402.2, C403.2, SW401.2, SW402.2, SW403.2, SW404.2, SW405.2, SW406.2, SW407.2, SW408.2, SW409.2, SW410.2, SW411.2, SW412.2, SW413.2, SW414.2, SW415.2, SW416.2, SW417.2, SW418.2, SW419.2, SW420.2, SW421.2, SW422.2, SW423.2, SW424.2, SW425.2, SW426.2, SW427.2, SW428.2, SW429.2, SW430.C, SW430.MP, SW430.S1, U401.8 (GND), U402.8 (GND), U403.8 (GND), U404.8 (GND), U405.2 (GND); also elsewhere on the board

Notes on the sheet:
400- Shift Register - Switch
